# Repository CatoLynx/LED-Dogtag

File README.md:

# LED Dogtag
Here you can find the hardware and software for my LED display dogtag.

# Repository Structure
* The `hardware/LED_Dogtag_HW` directory contains the hardware design and production files for the dogtag
* The `hardware/LED_Driver_Evaluation` directory contains the hardware design and production files for an evaluation/test board for the LED driver IC

## Licenses
The hardware part of this repository is licensed under the CERN Open Hardware Licence Version 2 - Strongly Reciprocal (CERN-OHL-S v2) or later.
The software part is licensed under the GNU General Public License v3 (GPLv3).

## Design Tools used
* Schematics and printed circuit board designs were made using KiCad 7
* 3D models were created using SolidWorks 2023

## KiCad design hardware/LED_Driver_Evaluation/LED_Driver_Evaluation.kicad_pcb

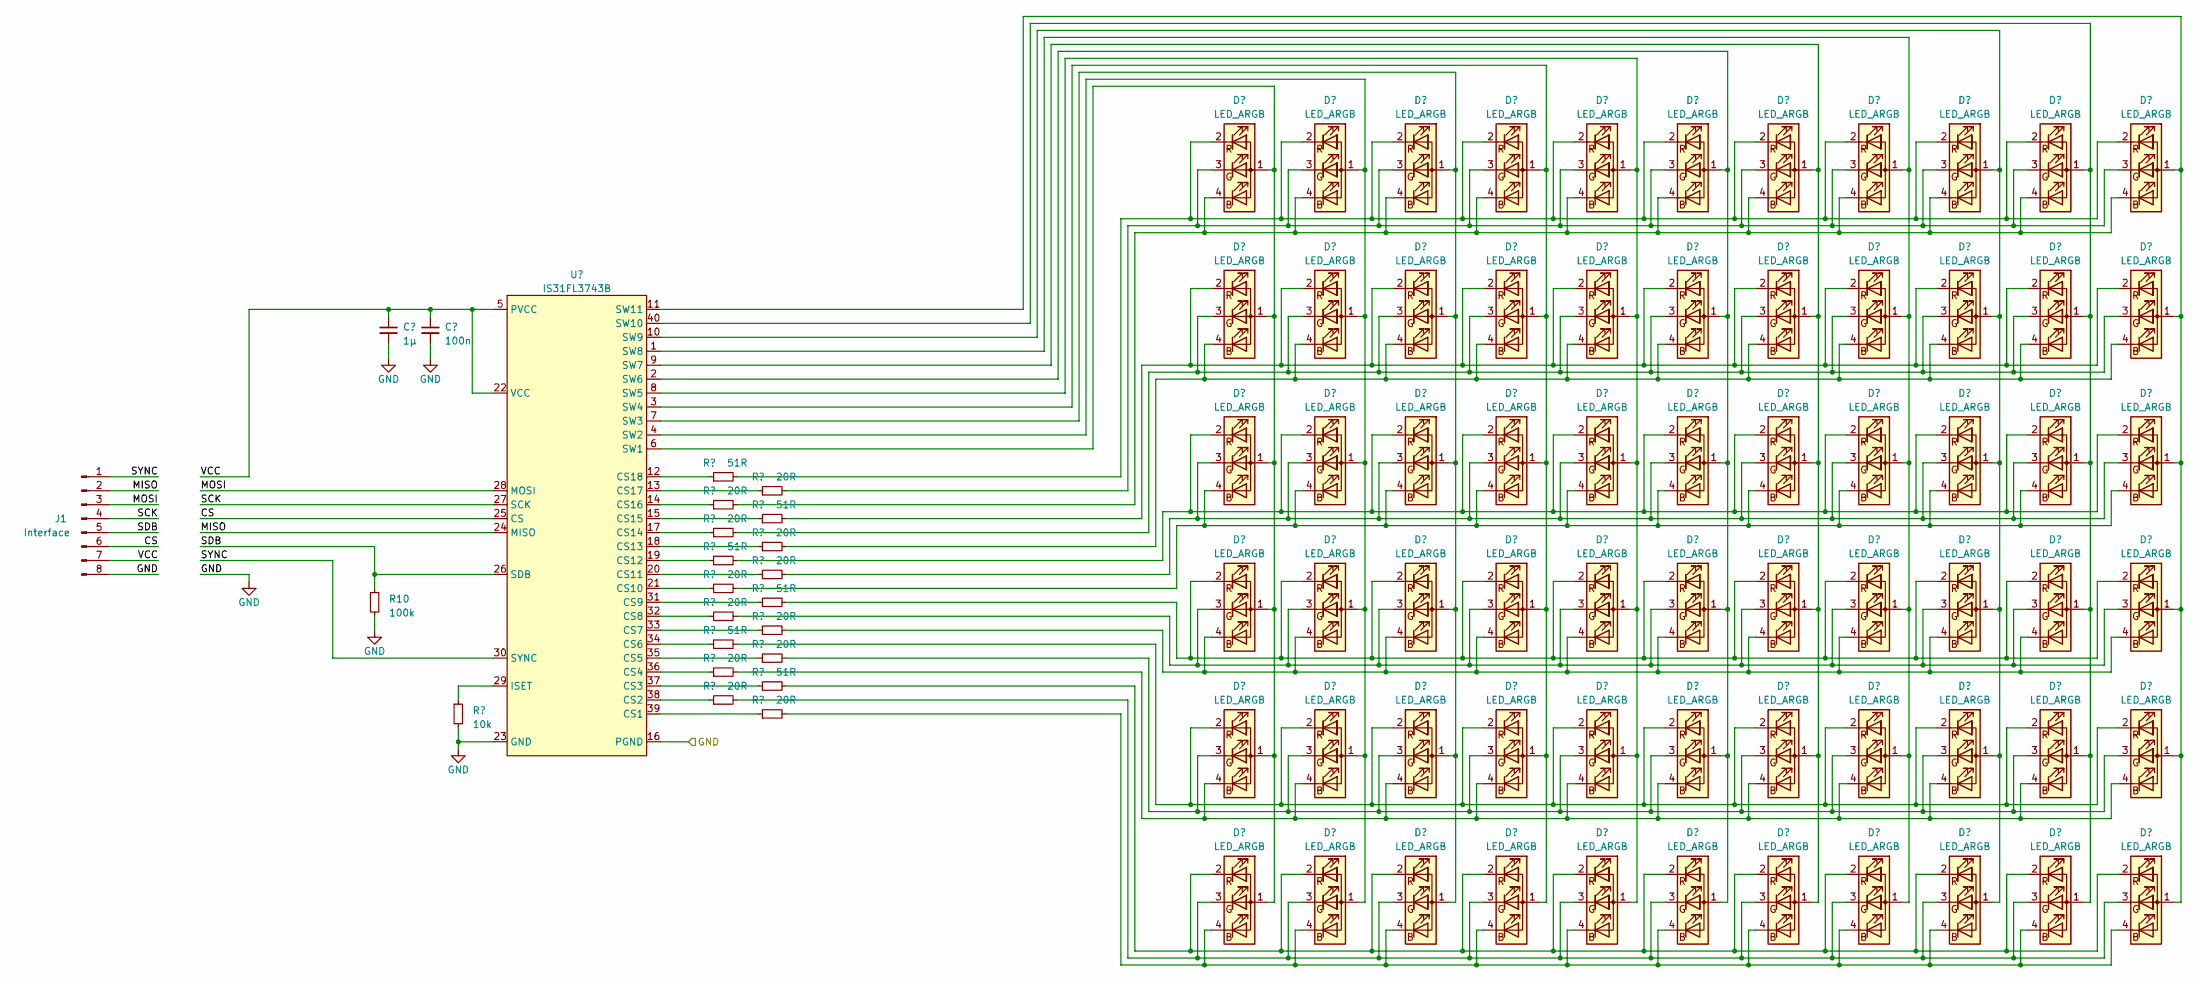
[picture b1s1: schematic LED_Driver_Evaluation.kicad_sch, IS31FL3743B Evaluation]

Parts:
C1: 1µ; C_0603_1608Metric
C2: 100n; C_0603_1608Metric
D1, D2, D3, D4, D5, D6, D7, D8, D9, D10, D11, D12, D13, D14, D15, D16, D17, D18, D19, D20, D21, D22, D23, D24, D25, D26, D27, D28, D29, D30, D31, D32, D33, D34, D35, D36, D37, D38, D39, D40, D41, D42, D43, D44, D45, D46, D47, D48, D49, D50, D51, D52, D53, D54, D55, D56, D57, D58, D59, D60, D61, D62, D63, D64, D65, D66: LED_ARGB; LED_0404
J1: Interface; PinHeader_1x08_P2.54mm_Vertical
R1, R4, R7, R11, R14, R17: 51R; R_0402_1005Metric
R2, R3, R5, R6, R8, R9, R12, R13, R15, R16, R18, R20: 20R; R_0402_1005Metric
R10: 100k; R_0603_1608Metric
R19: 10k; R_0402_1005Metric
U1: IS31FL3743B; UQFN-40-1EP_5x5mm_P0.4mm_EP3.8x3.8mm

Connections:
/CS: J1.6, U1.25 (CS)
/MISO: J1.2, U1.24 (MISO)
/MOSI: J1.3, U1.28 (MOSI)
/SCK: J1.4, U1.27 (SCK)
/SDB: J1.5, R10.1, U1.26 (SDB)
/SYNC: J1.1, U1.30 (SYNC)
/VCC: C1.1, C2.1, J1.7, U1.5 (PVCC), U1.22 (VCC)
GND: C1.2, C2.2, J1.8, R10.2, R19.2, U1.16 (PGND), U1.23 (GND), U1.41 (GND)
unnamed: D1.1 (A), D12.1 (A), D23.1 (A), D34.1 (A), D45.1 (A), D56.1 (A), U1.6 (SW1)
unnamed: D1.4 (BK), D2.4 (BK), D3.4 (BK), D4.4 (BK), D5.4 (BK), D6.4 (BK), D7.4 (BK), D8.4 (BK), D9.4 (BK), D10.4 (BK), D11.4 (BK), R3.2
unnamed: D1.3 (GK), D2.3 (GK), D3.3 (GK), D4.3 (GK), D5.3 (GK), D6.3 (GK), D7.3 (GK), D8.3 (GK), D9.3 (GK), D10.3 (GK), D11.3 (GK), R2.2
unnamed: D1.2 (RK), D2.2 (RK), D3.2 (RK), D4.2 (RK), D5.2 (RK), D6.2 (RK), D7.2 (RK), D8.2 (RK), D9.2 (RK), D10.2 (RK), D11.2 (RK), R1.2
unnamed: D10.1 (A), D21.1 (A), D32.1 (A), D43.1 (A), D54.1 (A), D65.1 (A), U1.40 (SW10)
unnamed: D11.1 (A), D22.1 (A), D33.1 (A), D44.1 (A), D55.1 (A), D66.1 (A), U1.11 (SW11)
unnamed: D12.4 (BK), D13.4 (BK), D14.4 (BK), D15.4 (BK), D16.4 (BK), D17.4 (BK), D18.4 (BK), D19.4 (BK), D20.4 (BK), D21.4 (BK), D22.4 (BK), R6.2
unnamed: D12.3 (GK), D13.3 (GK), D14.3 (GK), D15.3 (GK), D16.3 (GK), D17.3 (GK), D18.3 (GK), D19.3 (GK), D20.3 (GK), D21.3 (GK), D22.3 (GK), R5.2
unnamed: D12.2 (RK), D13.2 (RK), D14.2 (RK), D15.2 (RK), D16.2 (RK), D17.2 (RK), D18.2 (RK), D19.2 (RK), D20.2 (RK), D21.2 (RK), D22.2 (RK), R4.2
unnamed: D2.1 (A), D13.1 (A), D24.1 (A), D35.1 (A), D46.1 (A), D57.1 (A), U1.4 (SW2)
unnamed: D3.1 (A), D14.1 (A), D25.1 (A), D36.1 (A), D47.1 (A), D58.1 (A), U1.7 (SW3)
unnamed: D4.1 (A), D15.1 (A), D26.1 (A), D37.1 (A), D48.1 (A), D59.1 (A), U1.3 (SW4)
unnamed: D5.1 (A), D16.1 (A), D27.1 (A), D38.1 (A), D49.1 (A), D60.1 (A), U1.8 (SW5)
unnamed: D6.1 (A), D17.1 (A), D28.1 (A), D39.1 (A), D50.1 (A), D61.1 (A), U1.2 (SW6)
unnamed: D7.1 (A), D18.1 (A), D29.1 (A), D40.1 (A), D51.1 (A), D62.1 (A), U1.9 (SW7)
unnamed: D8.1 (A), D19.1 (A), D30.1 (A), D41.1 (A), D52.1 (A), D63.1 (A), U1.1 (SW8)
unnamed: D9.1 (A), D20.1 (A), D31.1 (A), D42.1 (A), D53.1 (A), D64.1 (A), U1.10 (SW9)
unnamed: D23.4 (BK), D24.4 (BK), D25.4 (BK), D26.4 (BK), D27.4 (BK), D28.4 (BK), D29.4 (BK), D30.4 (BK), D31.4 (BK), D32.4 (BK), D33.4 (BK), R9.2
unnamed: D23.3 (GK), D24.3 (GK), D25.3 (GK), D26.3 (GK), D27.3 (GK), D28.3 (GK), D29.3 (GK), D30.3 (GK), D31.3 (GK), D32.3 (GK), D33.3 (GK), R8.2
unnamed: D23.2 (RK), D24.2 (RK), D25.2 (RK), D26.2 (RK), D27.2 (RK), D28.2 (RK), D29.2 (RK), D30.2 (RK), D31.2 (RK), D32.2 (RK), D33.2 (RK), R7.2
unnamed: D34.4 (BK), D35.4 (BK), D36.4 (BK), D37.4 (BK), D38.4 (BK), D39.4 (BK), D40.4 (BK), D41.4 (BK), D42.4 (BK), D43.4 (BK), D44.4 (BK), R13.2
unnamed: D34.3 (GK), D35.3 (GK), D36.3 (GK), D37.3 (GK), D38.3 (GK), D39.3 (GK), D40.3 (GK), D41.3 (GK), D42.3 (GK), D43.3 (GK), D44.3 (GK), R12.2
unnamed: D34.2 (RK), D35.2 (RK), D36.2 (RK), D37.2 (RK), D38.2 (RK), D39.2 (RK), D40.2 (RK), D41.2 (RK), D42.2 (RK), D43.2 (RK), D44.2 (RK), R11.2
unnamed: D45.4 (BK), D46.4 (BK), D47.4 (BK), D48.4 (BK), D49.4 (BK), D50.4 (BK), D51.4 (BK), D52.4 (BK), D53.4 (BK), D54.4 (BK), D55.4 (BK), R16.2
unnamed: D45.3 (GK), D46.3 (GK), D47.3 (GK), D48.3 (GK), D49.3 (GK), D50.3 (GK), D51.3 (GK), D52.3 (GK), D53.3 (GK), D54.3 (GK), D55.3 (GK), R15.2
unnamed: D45.2 (RK), D46.2 (RK), D47.2 (RK), D48.2 (RK), D49.2 (RK), D50.2 (RK), D51.2 (RK), D52.2 (RK), D53.2 (RK), D54.2 (RK), D55.2 (RK), R14.2
unnamed: D56.4 (BK), D57.4 (BK), D58.4 (BK), D59.4 (BK), D60.4 (BK), D61.4 (BK), D62.4 (BK), D63.4 (BK), D64.4 (BK), D65.4 (BK), D66.4 (BK), R20.2
unnamed: D56.3 (GK), D57.3 (GK), D58.3 (GK), D59.3 (GK), D60.3 (GK), D61.3 (GK), D62.3 (GK), D63.3 (GK), D64.3 (GK), D65.3 (GK), D66.3 (GK), R18.2
unnamed: D56.2 (RK), D57.2 (RK), D58.2 (RK), D59.2 (RK), D60.2 (RK), D61.2 (RK), D62.2 (RK), D63.2 (RK), D64.2 (RK), D65.2 (RK), D66.2 (RK), R17.2
unnamed: R20.1, U1.39 (CS1)
unnamed: R18.1, U1.38 (CS2)
unnamed: R17.1, U1.37 (CS3)
unnamed: R16.1, U1.36 (CS4)
unnamed: R15.1, U1.35 (CS5)
unnamed: R14.1, U1.34 (CS6)
unnamed: R13.1, U1.33 (CS7)
unnamed: R12.1, U1.32 (CS8)
unnamed: R11.1, U1.31 (CS9)
unnamed: R9.1, U1.21 (CS10)
unnamed: R8.1, U1.20 (CS11)
unnamed: R7.1, U1.19 (CS12)
unnamed: R6.1, U1.18 (CS13)
unnamed: R5.1, U1.17 (CS14)
unnamed: R4.1, U1.15 (CS15)
unnamed: R3.1, U1.14 (CS16)
unnamed: R2.1, U1.13 (CS17)
unnamed: R1.1, U1.12 (CS18)
unnamed: R19.1, U1.29 (ISET)

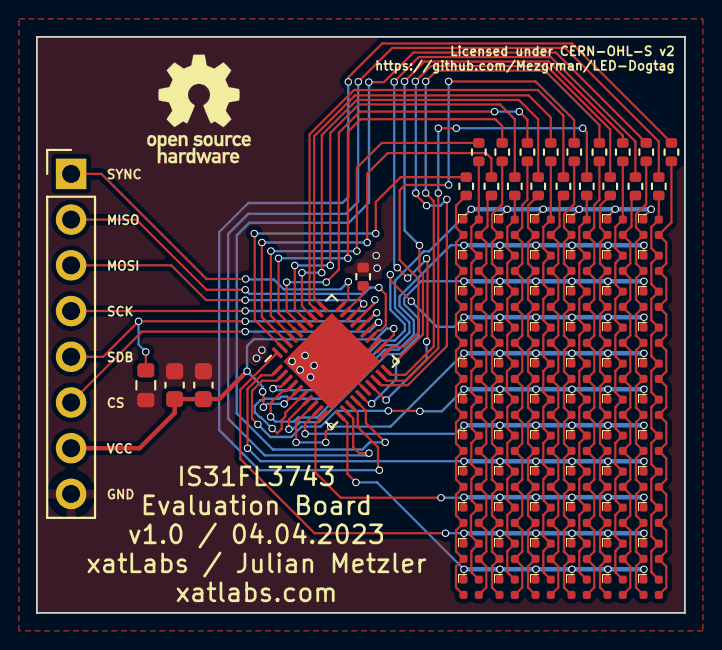
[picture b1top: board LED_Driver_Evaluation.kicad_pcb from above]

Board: 2 copper layers, 36.0 x 32.0 mm, 90 parts (0 on the bottom side), 56 nets.

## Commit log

2023-04-05 Initial commit containing the LED driver evaluation board
2023-04-23 Add production files for LED driver evaluation board
2023-04-23 Add Arduino test software for IS31FL3743 evaluation board

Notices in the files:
hardware/LED_Driver_Evaluation/LED_Driver_Evaluation.kicad_pcb:
Licensed under CERN-OHL-S v2
